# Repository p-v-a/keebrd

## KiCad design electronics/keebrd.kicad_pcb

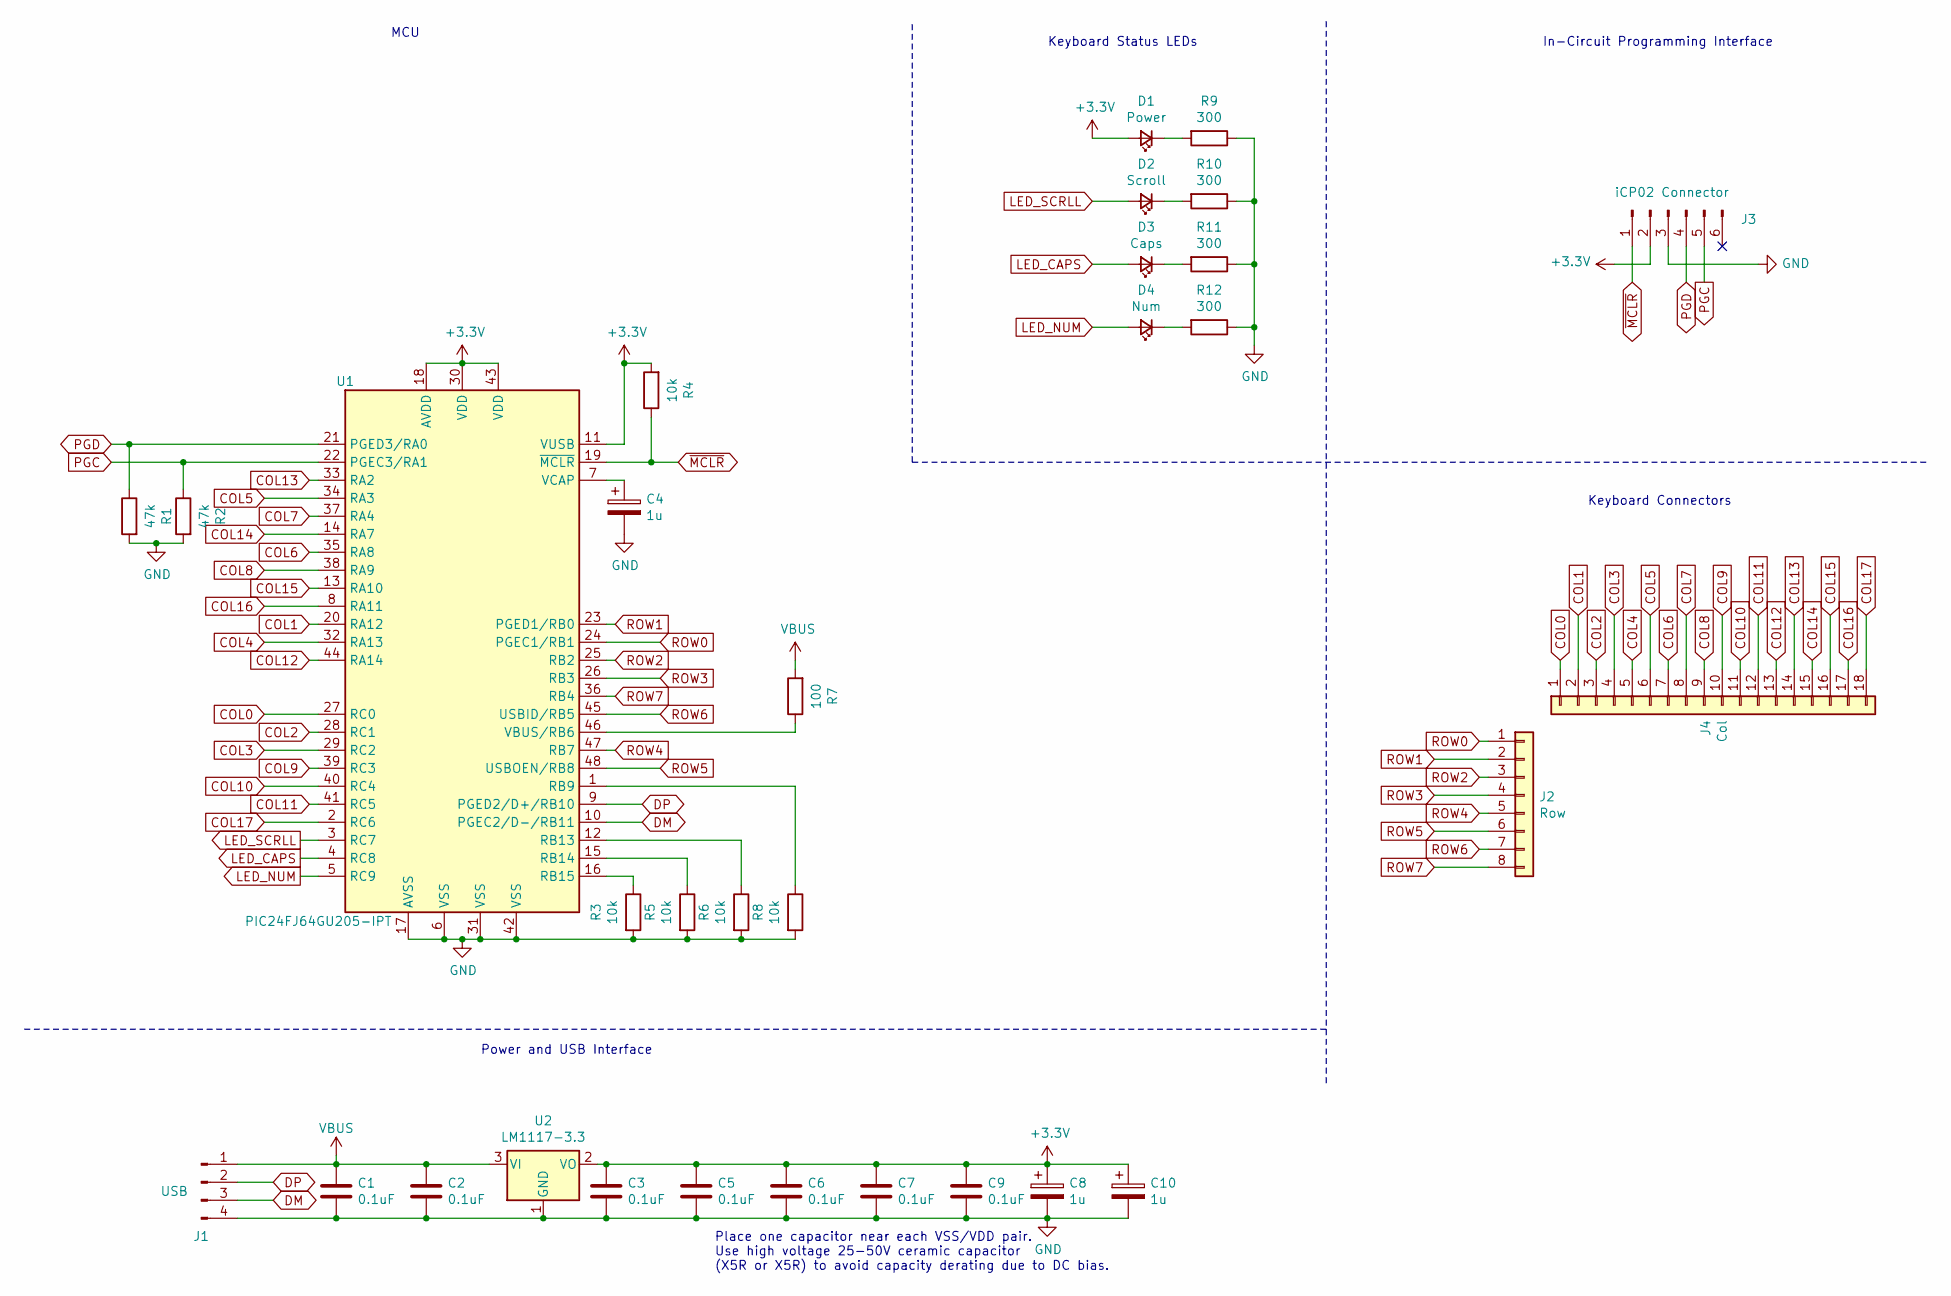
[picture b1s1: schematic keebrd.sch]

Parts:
C1, C2, C3, C5, C6, C7, C9: 0.1uF; C_0603_1608Metric_Pad1.08x0.95mm_HandSolder
C4, C8: 1u; C_0805_2012Metric
C10: 1u; CP_Radial_D5.0mm_P2.50mm
D1: Power; LED_0805_2012Metric_Pad1.15x1.40mm_HandSolder
D2: Scroll; LED_D1.8mm_W3.3mm_H2.4mm
D3: Caps; LED_D1.8mm_W3.3mm_H2.4mm
D4: Num; LED_D1.8mm_W3.3mm_H2.4mm
J1: USB; PinHeader_1x04_P2.00mm_Horizontal
J2: Row; TE_84952-8_1x08-1MP_P1.0mm_Horizontal
J3: iCP02 Connector; PinHeader_1x06_P1.27mm_Vertical
J4: Col; TE_1-84953-8_1x18-1MP_P1.0mm_Horizontal
R1, R2: 47k; R_0603_1608Metric_Pad0.98x0.95mm_HandSolder
R3, R4, R5, R6, R8: 10k; R_0603_1608Metric_Pad0.98x0.95mm_HandSolder
R7: 100; R_0603_1608Metric_Pad0.98x0.95mm_HandSolder
R9, R10, R11, R12: 300; R_0603_1608Metric_Pad0.98x0.95mm_HandSolder
U1: PIC24FJ64GU205-IPT; TQFP-48_7x7mm_P0.5mm
U2: LM1117-3.3; SOT-223-3_TabPin2

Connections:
+3V3: C3.1, C5.1, C6.1, C7.1, C8.1, C9.1, C10.1, D1.2 (A), J3.2, R4.2, U1.11 (VUSB), U1.18 (AVDD), U1.30 (VDD), U1.43 (VDD), U2.2 (VO)
COL0: J4.1, U1.27 (RC0)
COL1: J4.2, U1.20 (RA12)
COL2: J4.3, U1.28 (RC1)
COL3: J4.4, U1.29 (RC2)
COL4: J4.5, U1.32 (RA13)
COL5: J4.6, U1.34 (RA3)
COL6: J4.7, U1.35 (RA8)
COL7: J4.8, U1.37 (RA4)
COL8: J4.9, U1.38 (RA9)
COL9: J4.10, U1.39 (RC3)
COL10: J4.11, U1.40 (RC4)
COL11: J4.12, U1.41 (RC5)
COL12: J4.13, U1.44 (RA14)
COL13: J4.14, U1.33 (RA2)
COL14: J4.15, U1.14 (RA7)
COL15: J4.16, U1.13 (RA10)
COL16: J4.17, U1.8 (RA11)
COL17: J4.18, U1.2 (RC6)
DM: J1.3, U1.10 (PGEC2/D-/RB11)
DP: J1.2, U1.9 (PGED2/D+/RB10)
GND: C1.2, C2.2, C3.2, C4.2, C5.2, C6.2, C7.2, C8.2, C9.2, C10.2, J1.4, J3.3, R1.2, R2.2, R3.2, R5.2, R6.2, R8.2, R9.1, R10.1, R11.1, R12.1, U1.6 (VSS), U1.17 (AVSS), U1.31 (VSS), U1.42 (VSS), U2.1 (GND)
LED_CAPS: D3.2 (A), U1.4 (RC8)
LED_NUM: D4.2 (A), U1.5 (RC9)
LED_SCRLL: D2.2 (A), U1.3 (RC7)
unnamed: C4.1, U1.7 (VCAP)
unnamed: D1.1 (K), R9.2
unnamed: D2.1 (K), R10.2
unnamed: D3.1 (K), R11.2
unnamed: D4.1 (K), R12.2
unnamed: R3.1, U1.16 (RB15)
unnamed: R5.1, U1.15 (RB14)
unnamed: R6.1, U1.12 (RB13)
unnamed: R7.1, U1.46 (VBUS/RB6)
unnamed: R8.1, U1.1 (RB9)
PGC: J3.5, R2.1, U1.22 (PGEC3/RA1)
PGD: J3.4, R1.1, U1.21 (PGED3/RA0)
ROW0: J2.1, U1.24 (PGEC1/RB1)
ROW1: J2.2, U1.23 (PGED1/RB0)
ROW2: J2.3, U1.25 (RB2)
ROW3: J2.4, U1.26 (RB3)
ROW4: J2.5, U1.47 (RB7)
ROW5: J2.6, U1.48 (USBOEN/RB8)
ROW6: J2.7, U1.45 (USBID/RB5)
ROW7: J2.8, U1.36 (RB4)
VBUS: C1.1, C2.1, J1.1, R7.2, U2.3 (VI)
~MCLR: J3.1, R4.1, U1.19 (~MCLR)

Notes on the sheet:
In-Circuit Programming Interface
Keyboard Connectors
Keyboard Status LEDs
MCU
Power and USB Interface
Place one capacitor near each VSS/VDD pair. Use high voltage 25-50V ceramic capacitor (X5R or X5R) to avoid capacity derating due to DC bias.

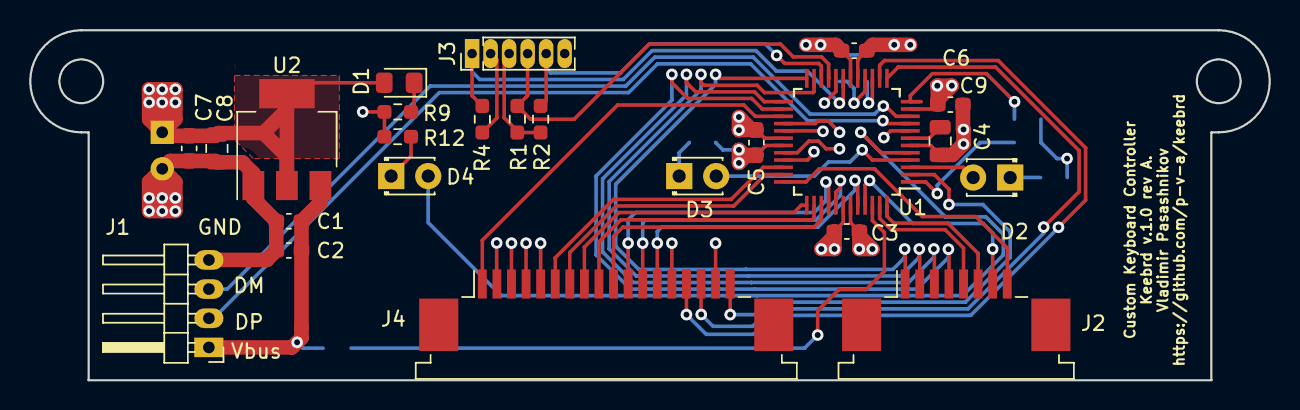
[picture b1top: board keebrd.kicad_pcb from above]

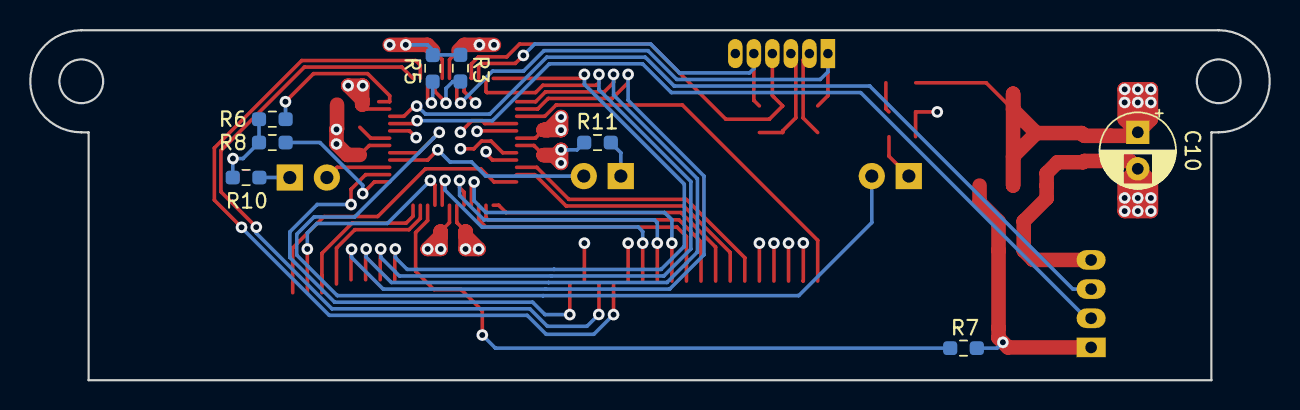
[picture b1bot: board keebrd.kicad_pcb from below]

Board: 4 copper layers, 85.0 x 24.0 mm, 32 parts (8 on the bottom side), 47 nets.

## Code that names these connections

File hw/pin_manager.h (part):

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*/
/**
  @Summary
    Sets the GPIO pin, RA10, high using LATA10.

  @Description
    Sets the GPIO pin, RA10, high using LATA10.

  @Preconditions
    The RA10 must be set to an output.
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#define COL15_SetHigh()          (_LATA10 = 1)
/**
  @Summary
    Sets the GPIO pin, RA10, low using LATA10.

  @Description
    Sets the GPIO pin, RA10, low using LATA10.

  @Preconditions
    The RA10 must be set to an output.
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#define COL15_SetLow()           (_LATA10 = 0)
/**
  @Summary
    Toggles the GPIO pin, RA10, using LATA10.

  @Description
    Toggles the GPIO pin, RA10, using LATA10.

  @Preconditions
    The RA10 must be set to an output.
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#define COL15_Toggle()           (_LATA10 ^= 1)
/**
  @Summary
    Reads the value of the GPIO pin, RA10.

  @Description
    Reads the value of the GPIO pin, RA10.

  @Preconditions
    None.
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    </code>

*/
#define COL15_GetValue()         _RA10
/**
  @Summary
    Configures the GPIO pin, RA10, as an input.

  @Description
    Configures the GPIO pin, RA10, as an input.

  @Preconditions
    None.
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#define COL15_SetDigitalInput()  (_TRISA10 = 1)
/**
  @Summary
    Configures the GPIO pin, RA10, as an output.

  @Description
    Configures the GPIO pin, RA10, as an output.

  @Preconditions
    None.
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#define COL15_SetDigitalOutput() (_TRISA10 = 0)
/**
  @Summary
    Sets the GPIO pin, RA11, high using LATA11.

  @Description
    Sets the GPIO pin, RA11, high using LATA11.

  @Preconditions
    The RA11 must be set to an output.
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#define COL16_SetHigh()          (_LATA11 = 1)
/**
  @Summary
    Sets the GPIO pin, RA11, low using LATA11.

  @Description
    Sets the GPIO pin, RA11, low using LATA11.

  @Preconditions
    The RA11 must be set to an output.
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#define COL16_SetLow()           (_LATA11 = 0)
/**
  @Summary
    Toggles the GPIO pin, RA11, using LATA11.

  @Description
    Toggles the GPIO pin, RA11, using LATA11.

  @Preconditions
    The RA11 must be set to an output.
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#define COL16_Toggle()           (_LATA11 ^= 1)
/**
  @Summary
    Reads the value of the GPIO pin, RA11.

  @Description
    Reads the value of the GPIO pin, RA11.

  @Preconditions
    None.
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    </code>

*/
#define COL16_GetValue()         _RA11
/**
  @Summary
    Configures the GPIO pin, RA11, as an input.

  @Description
    Configures the GPIO pin, RA11, as an input.

  @Preconditions
    None.
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#define COL16_SetDigitalInput()  (_TRISA11 = 1)
/**
  @Summary
    Configures the GPIO pin, RA11, as an output.

  @Description
    Configures the GPIO pin, RA11, as an output.

  @Preconditions
    None.
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#define COL16_SetDigitalOutput() (_TRISA11 = 0)
/**
  @Summary
    Sets the GPIO pin, RA12, high using LATA12.

  @Description
    Sets the GPIO pin, RA12, high using LATA12.

  @Preconditions
    The RA12 must be set to an output.
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#define COL1_SetHigh()          (_LATA12 = 1)
/**
  @Summary
    Sets the GPIO pin, RA12, low using LATA12.

  @Description
    Sets the GPIO pin, RA12, low using LATA12.

  @Preconditions
    The RA12 must be set to an output.
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#define COL1_SetLow()           (_LATA12 = 0)
/**
  @Summary
    Toggles the GPIO pin, RA12, using LATA12.

  @Description
    Toggles the GPIO pin, RA12, using LATA12.

  @Preconditions
    The RA12 must be set to an output.
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#define COL1_Toggle()           (_LATA12 ^= 1)
/**
  @Summary
    Reads the value of the GPIO pin, RA12.

  @Description
    Reads the value of the GPIO pin, RA12.

  @Preconditions
    None.
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    </code>

*/
#define COL1_GetValue()         _RA12
/**
  @Summary
    Configures the GPIO pin, RA12, as an input.

  @Description
    Configures the GPIO pin, RA12, as an input.

  @Preconditions
    None.
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#define COL1_SetDigitalInput()  (_TRISA12 = 1)
/**
  @Summary
    Configures the GPIO pin, RA12, as an output.

  @Description
    Configures the GPIO pin, RA12, as an output.

  @Preconditions
    None.
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#define COL1_SetDigitalOutput() (_TRISA12 = 0)
/**
  @Summary
    Sets the GPIO pin, RA13, high using LATA13.

  @Description
    Sets the GPIO pin, RA13, high using LATA13.

  @Preconditions
    The RA13 must be set to an output.
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#define COL4_SetHigh()          (_LATA13 = 1)
/**
  @Summary
    Sets the GPIO pin, RA13, low using LATA13.

  @Description
    Sets the GPIO pin, RA13, low using LATA13.

  @Preconditions
    The RA13 must be set to an output.
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#define COL4_SetLow()           (_LATA13 = 0)
/**
  @Summary
    Toggles the GPIO pin, RA13, using LATA13.

  @Description
    Toggles the GPIO pin, RA13, using LATA13.

  @Preconditions
    The RA13 must be set to an output.
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#define COL4_Toggle()           (_LATA13 ^= 1)
/**
  @Summary
    Reads the value of the GPIO pin, RA13.

  @Description
    Reads the value of the GPIO pin, RA13.

  @Preconditions
    None.
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    </code>

*/
#define COL4_GetValue()         _RA13
/**
  @Summary
    Configures the GPIO pin, RA13, as an input.

  @Description
    Configures the GPIO pin, RA13, as an input.

  @Preconditions
    None.
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#define COL4_SetDigitalInput()  (_TRISA13 = 1)
/**
  @Summary
    Configures the GPIO pin, RA13, as an output.

  @Description
    Configures the GPIO pin, RA13, as an output.

  @Preconditions
    None.
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#define COL4_SetDigitalOutput() (_TRISA13 = 0)
/**
  @Summary
    Sets the GPIO pin, RA14, high using LATA14.

  @Description
    Sets the GPIO pin, RA14, high using LATA14.

  @Preconditions
    The RA14 must be set to an output.
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#define COL12_SetHigh()          (_LATA14 = 1)
/**
  @Summary
    Sets the GPIO pin, RA14, low using LATA14.

  @Description
    Sets the GPIO pin, RA14, low using LATA14.

  @Preconditions
    The RA14 must be set to an output.
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#define COL12_SetLow()           (_LATA14 = 0)
/**
  @Summary
    Toggles the GPIO pin, RA14, using LATA14.

  @Description
    Toggles the GPIO pin, RA14, using LATA14.

  @Preconditions
    The RA14 must be set to an output.
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#define COL12_Toggle()           (_LATA14 ^= 1)
/**
  @Summary
    Reads the value of the GPIO pin, RA14.

  @Description
    Reads the value of the GPIO pin, RA14.

  @Preconditions
    None.
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    </code>

*/
#define COL12_GetValue()         _RA14
/**
  @Summary
    Configures the GPIO pin, RA14, as an input.

  @Description
    Configures the GPIO pin, RA14, as an input.

  @Preconditions
    None.
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#define COL12_SetDigitalInput()  (_TRISA14 = 1)
/**
  @Summary
    Configures the GPIO pin, RA14, as an output.

  @Description
    Configures the GPIO pin, RA14, as an output.

  @Preconditions
    None.
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#define COL12_SetDigitalOutput() (_TRISA14 = 0)
/**
  @Summary
    Sets the GPIO pin, RA2, high using LATA2.

  @Description
    Sets the GPIO pin, RA2, high using LATA2.

  @Preconditions
    The RA2 must be set to an output.
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#define COL13_SetHigh()          (_LATA2 = 1)
/**
  @Summary
    Sets the GPIO pin, RA2, low using LATA2.

  @Description
    Sets the GPIO pin, RA2, low using LATA2.

  @Preconditions
    The RA2 must be set to an output.
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#define COL13_SetLow()           (_LATA2 = 0)
/**
  @Summary
    Toggles the GPIO pin, RA2, using LATA2.

  @Description
    Toggles the GPIO pin, RA2, using LATA2.

  @Preconditions
    The RA2 must be set to an output.
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#define COL13_Toggle()           (_LATA2 ^= 1)
/**
  @Summary
    Reads the value of the GPIO pin, RA2.

  @Description
    Reads the value of the GPIO pin, RA2.

  @Preconditions
    None.
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    </code>

*/
#define COL13_GetValue()         _RA2
/**
  @Summary
    Configures the GPIO pin, RA2, as an input.

  @Description
    Configures the GPIO pin, RA2, as an input.

  @Preconditions
    None.
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#define COL13_SetDigitalInput()  (_TRISA2 = 1)
/**
  @Summary
    Configures the GPIO pin, RA2, as an output.

  @Description
    Configures the GPIO pin, RA2, as an output.

  @Preconditions
    None.
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#define COL13_SetDigitalOutput() (_TRISA2 = 0)
/**
  @Summary
    Sets the GPIO pin, RA3, high using LATA3.

  @Description
    Sets the GPIO pin, RA3, high using LATA3.

  @Preconditions
    The RA3 must be set to an output.
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#define COL5_SetHigh()          (_LATA3 = 1)
/**
  @Summary
    Sets the GPIO pin, RA3, low using LATA3.

  @Description
    Sets the GPIO pin, RA3, low using LATA3.

  @Preconditions
    The RA3 must be set to an output.
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#define COL5_SetLow()           (_LATA3 = 0)
/**
  @Summary
    Toggles the GPIO pin, RA3, using LATA3.

  @Description
    Toggles the GPIO pin, RA3, using LATA3.

  @Preconditions
    The RA3 must be set to an output.
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#define COL5_Toggle()           (_LATA3 ^= 1)
/**
  @Summary
    Reads the value of the GPIO pin, RA3.

  @Description
    Reads the value of the GPIO pin, RA3.

  @Preconditions
    None.
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    </code>

*/
#define COL5_GetValue()         _RA3
/**
  @Summary
    Configures the GPIO pin, RA3, as an input.

  @Description
    Configures the GPIO pin, RA3, as an input.

  @Preconditions
    None.
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#define COL5_SetDigitalInput()  (_TRISA3 = 1)
/**
  @Summary
    Configures the GPIO pin, RA3, as an output.

  @Description
    Configures the GPIO pin, RA3, as an output.

  @Preconditions
    None.
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#define COL5_SetDigitalOutput() (_TRISA3 = 0)
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
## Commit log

2021-10-28 add schematics and PCB

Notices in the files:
hw/pin_manager.h:
(c) 2020 Microchip Technology Inc. and its subsidiaries. You may use this
